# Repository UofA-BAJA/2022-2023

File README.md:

# Electrical Team 2022-2023
This is the codebase for the University of Arizona BAJA Electrical Team, year 2022/2023.

[Google Drive Link](https://drive.google.com/drive/folders/1pqr16L63S9_5N_NZjZeFR-gvrg_NTns5?usp=sharing)

**This years officers and members include:**
Alex Romero (Electrical Lead),
Michael Byerly (Father),
Oliver Sjostrom,
Alyssa Pomerleau,
Henry Overbeck,
Liam Neu,
Muthu Krishnappan,
Man Doan,
Aeden Grandinetti,
Dorian Shay,
Aliah Haigh,
Juliana Levy
...

**Languages include:**
Python (Ground Station Systems),
C++ (Telemetry System),

Pull Requests into the Main Branch can be approved by Alex or Michael.
We also have a Codigna review bot that will automatically grade our code and offer suggestions in order to improve performance or legibility.

If you have any questions regarding any pieces of software or their functionality, please reach out to the officers.

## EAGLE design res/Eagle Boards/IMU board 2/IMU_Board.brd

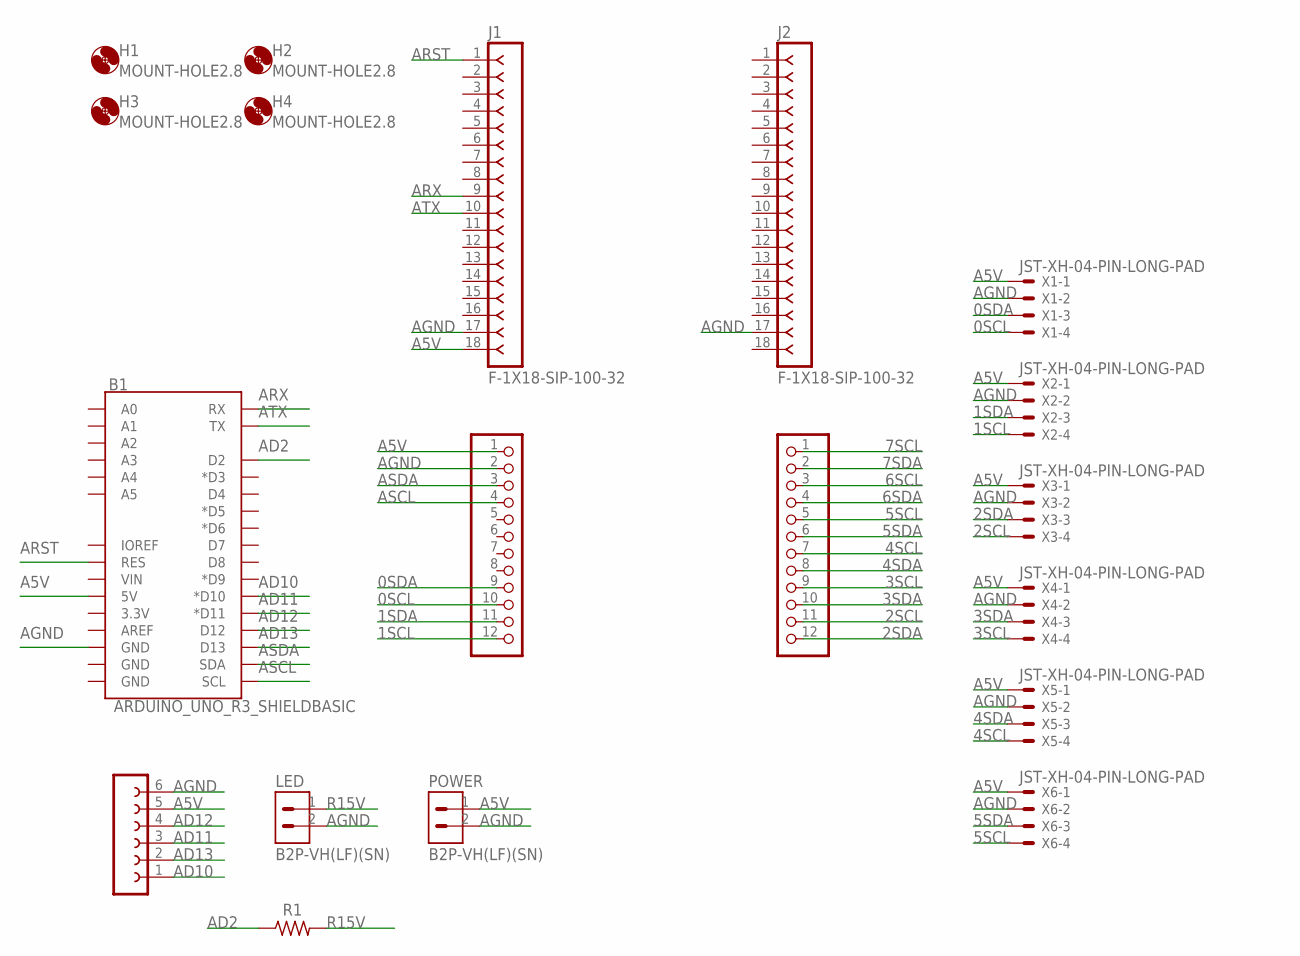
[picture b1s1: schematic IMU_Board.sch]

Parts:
B1: ARDUINO_UNO_R3_SHIELDBASIC; UNO_R3_SHIELD
H1, H2, H3, H4: MOUNT-HOLE2.8; 2,8
J1, J2: F-1X18-SIP-100-32; SIP-100-18-32
JP1, JP3: HEADER-1X12; 1X12_ROUND
LED: B2P-VH(LF)(SN); HDR-02
POWER: B2P-VH(LF)(SN); HDR-02
R1: R-US_AXIAL-11.7MM-PITCH; RESAD1176W63L850D250B
SD: FE06-1; FE06
X1, X2, X3, X4, X5, X6: JST-XH-04-PIN-LONG-PAD; JST-XH-04-PACKAGE-LONG-PAD

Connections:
0SCL: JP3.10, X1.4
0SDA: JP3.9, X1.3
1SCL: JP3.12, X2.4
1SDA: JP3.11, X2.3
2SCL: JP1.11, X3.4
2SDA: JP1.12, X3.3
3SCL: JP1.9, X4.4
3SDA: JP1.10, X4.3
4SCL: JP1.7, X5.4
4SDA: JP1.8, X5.3
5SCL: JP1.5, X6.4
5SDA: JP1.6, X6.3
6SCL: JP1.3
6SDA: JP1.4
7SCL: JP1.1
7SDA: JP1.2
A5V: B1.5V, J1.18, JP3.1, POWER.1, SD.5, X1.1, X2.1, X3.1, X4.1, X5.1, X6.1
AD2: B1.D2, R1.1
AD10: B1.D10 (*D10), SD.1
AD11: B1.D11 (*D11), SD.3
AD12: B1.D12, SD.4
AD13: B1.D13, SD.2
AGND: B1.GND@2 (GND), J1.17, J2.17, JP3.2, LED.2, POWER.2, SD.6, X1.2, X2.2, X3.2, X4.2, X5.2, X6.2
ARST: B1.RES, J1.1
ARX: B1.RX, J1.9
ASCL: B1.SCL, JP3.4
ASDA: B1.SDA, JP3.3
ATX: B1.TX, J1.10
R15V: LED.1, R1.2

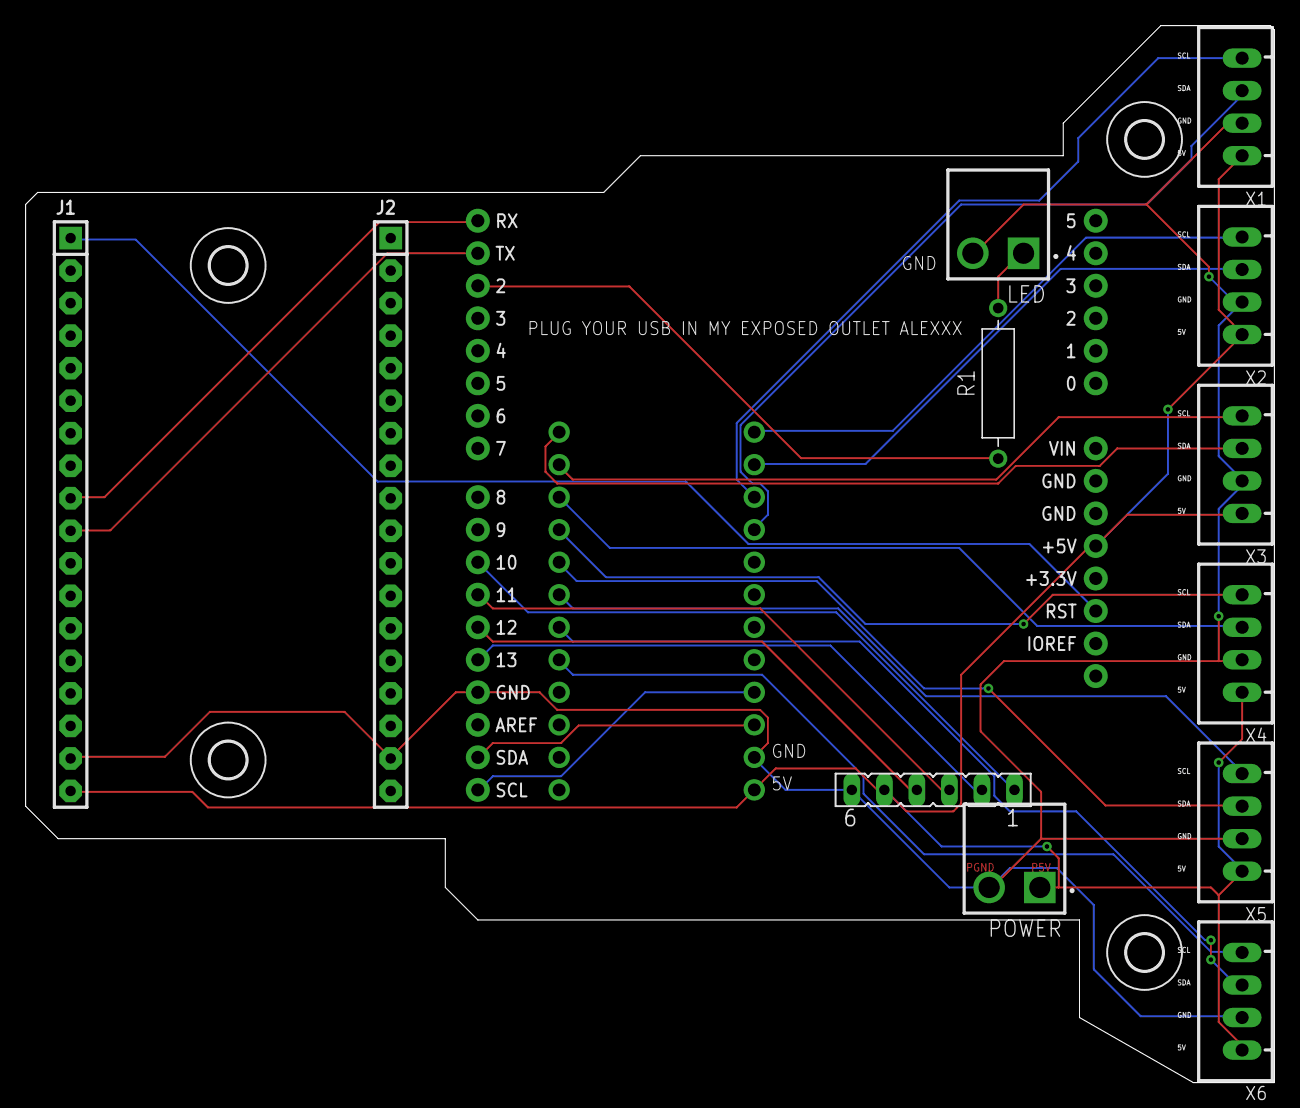
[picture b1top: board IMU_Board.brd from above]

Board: 2 copper layers, 97.5 x 82.5 mm, 19 parts (0 on the bottom side), 25 nets.

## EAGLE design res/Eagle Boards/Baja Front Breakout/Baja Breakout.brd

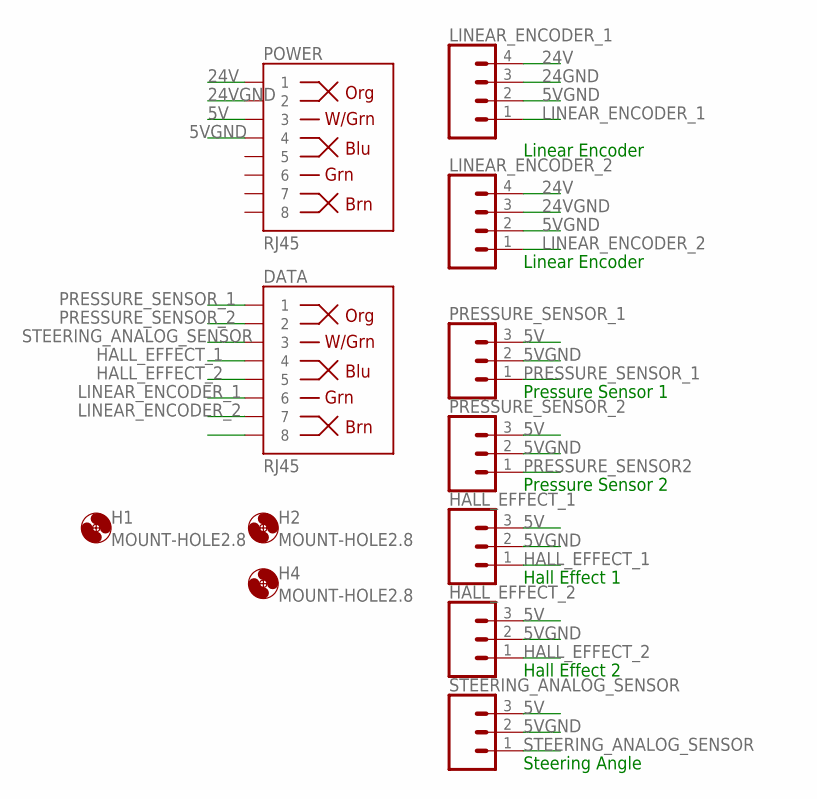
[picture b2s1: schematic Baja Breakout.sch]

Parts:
DATA: RJ45; RJ45-8
H1, H2, H4: MOUNT-HOLE2.8; 2,8
HALL_EFFECT_1, HALL_EFFECT_2: CONN_03; 1X03
LINEAR_ENCODER_1, LINEAR_ENCODER_2: CONN_04; 1X04
POWER: RJ45; RJ45-8
PRESSURE_SENSOR_1, PRESSURE_SENSOR_2: CONN_03; 1X03
STEERING_ANALOG_SENSOR: CONN_03; 1X03

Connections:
5V: HALL_EFFECT_1.3, HALL_EFFECT_2.3, POWER.3, PRESSURE_SENSOR_1.3, PRESSURE_SENSOR_2.3, STEERING_ANALOG_SENSOR.3
5VGND: HALL_EFFECT_1.2, HALL_EFFECT_2.2, LINEAR_ENCODER_1.2, LINEAR_ENCODER_2.2, POWER.4, PRESSURE_SENSOR_1.2, PRESSURE_SENSOR_2.2, STEERING_ANALOG_SENSOR.2
24GND: LINEAR_ENCODER_1.3
24V: LINEAR_ENCODER_1.4, LINEAR_ENCODER_2.4, POWER.1
24VGND: LINEAR_ENCODER_2.3, POWER.2
HALL_EFFECT_1: DATA.4, HALL_EFFECT_1.1
HALL_EFFECT_2: DATA.5, HALL_EFFECT_2.1
LINEAR_ENCODER_1: DATA.6, LINEAR_ENCODER_1.1
LINEAR_ENCODER_2: DATA.7, LINEAR_ENCODER_2.1
PRESSURE_SENSOR2: PRESSURE_SENSOR_2.1
PRESSURE_SENSOR_1: DATA.1, PRESSURE_SENSOR_1.1
PRESSURE_SENSOR_2: DATA.2
STEERING_ANALOG_SENSOR: DATA.3, STEERING_ANALOG_SENSOR.1

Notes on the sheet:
Linear Encoder
Pressure Sensor 2
Hall Effect 1
Hall Effect 2
Steering Angle
Pressure Sensor 1

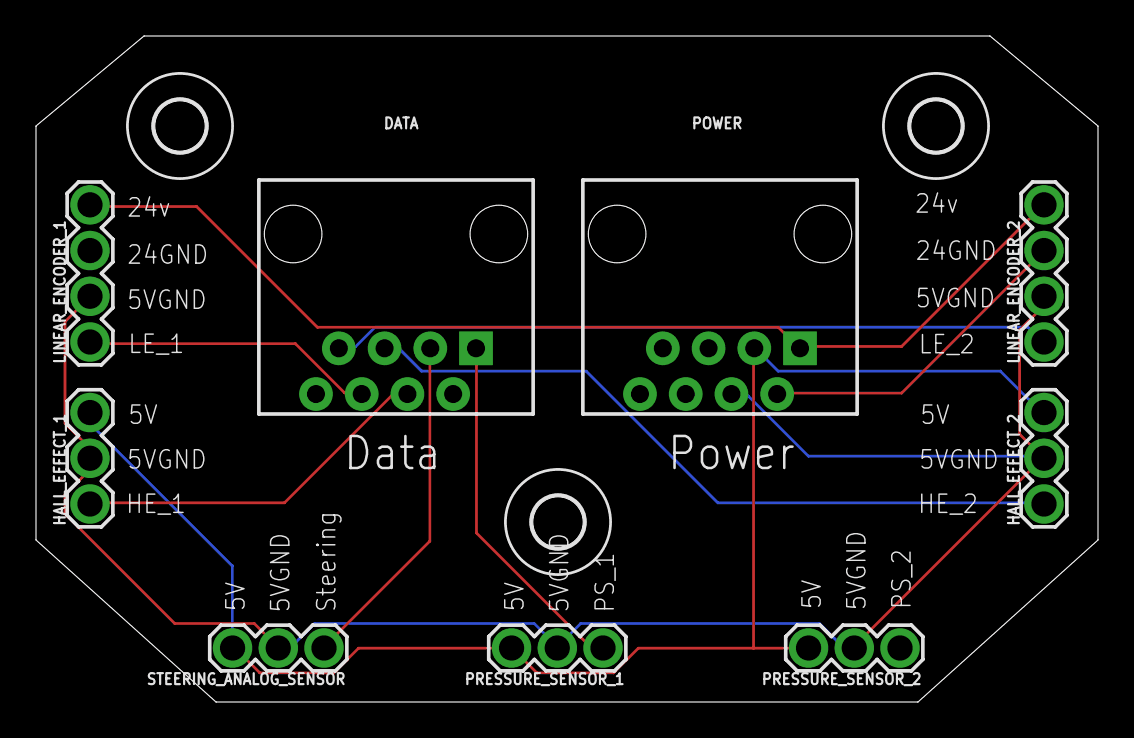
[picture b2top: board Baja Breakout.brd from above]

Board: 2 copper layers, 59.0 x 37.0 mm, 12 parts (0 on the bottom side), 10 nets.

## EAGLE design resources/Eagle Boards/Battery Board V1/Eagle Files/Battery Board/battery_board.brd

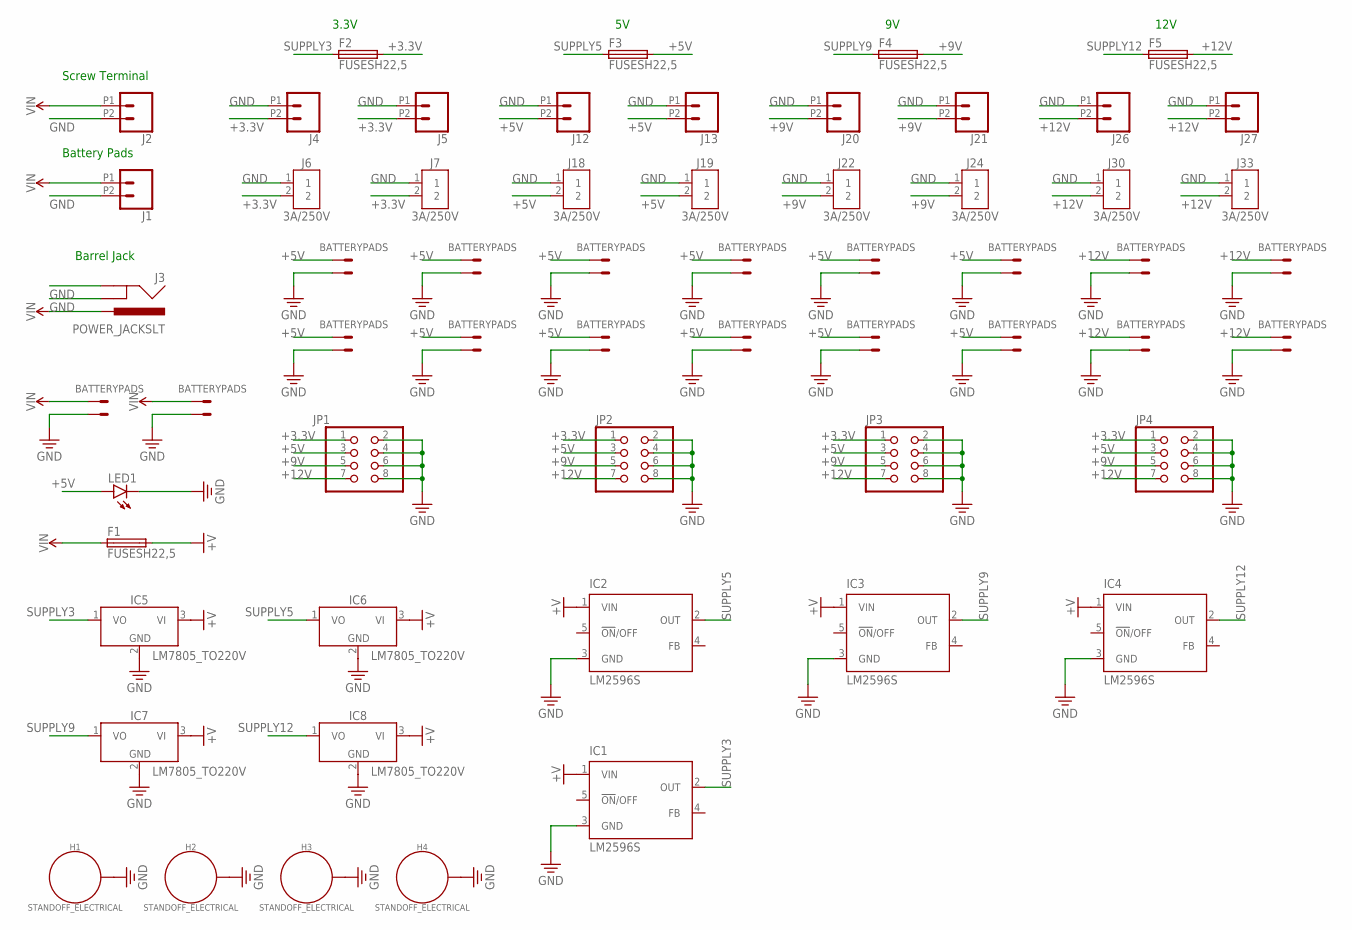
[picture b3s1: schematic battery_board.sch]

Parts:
BATTERY1, BATTERY2: BATTERYPADS; DIODFN1228X508X30-2N
F1, F2, F3, F4, F5: FUSESH22,5; SH22,5
H1, H2, H3, H4: STANDOFF_ELECTRICAL; STANDOFF-ELECTRICAL
IC1, IC2, IC3, IC4: LM2596S; TO263-5
IC5, IC6, IC7, IC8: LM7805_TO220V; TO220V
J1, J2, J4, J5, J12, J13, J20, J21, J26, J27: CONN_022.54MM_SCREWTERM; 1X02_2.54_SCREWTERM
J3: POWER_JACKSLT; POWER_JACK_SLOT
J6, J7, J18, J19, J22, J24, J30, J33: 3A/250V; B2B-XH-A
JP1, JP2, JP3, JP4: PINHD-2X4; 2X04
LED1: LEDCHIP-LED0805; CHIP-LED0805
U$1, U$2, U$3, U$4, U$5, U$6, U$7, U$8, U$9, U$10, U$11, U$12, U$13, U$14, U$15, U$16: BATTERYPADS; DIODFN1228X508X30-2N

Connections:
+3.3V: F2.2, J4.P2 (2), J5.P2 (2), J6.2, J7.2, JP1.1, JP2.1, JP3.1, JP4.1
+5V: F3.2, J12.P2 (2), J13.P2 (2), J18.2, J19.2, JP1.3, JP2.3, JP3.3, JP4.3, LED1.A, U$1.VIN, U$2.VIN, U$3.VIN, U$4.VIN, U$5.VIN, U$6.VIN, U$7.VIN, U$8.VIN, U$13.VIN, U$14.VIN, U$15.VIN, U$16.VIN
+9V: F4.2, J20.P2 (2), J21.P2 (2), J22.2, J24.2, JP1.5, JP2.5, JP3.5, JP4.5
+12V: F5.2, J26.P2 (2), J27.P2 (2), J30.2, J33.2, JP1.7, JP2.7, JP3.7, JP4.7, U$9.VIN, U$10.VIN, U$11.VIN, U$12.VIN
+V: F1.2, IC1.1 (VIN), IC2.1 (VIN), IC3.1 (VIN), IC4.1 (VIN), IC5.3 (VI), IC6.3 (VI), IC7.3 (VI), IC8.3 (VI)
GND: BATTERY1.GND, BATTERY2.GND, H1.P1, H2.P1, H3.P1, H4.P1, IC1.3 (GND), IC2.3 (GND), IC3.3 (GND), IC4.3 (GND), IC5.2 (GND), IC6.2 (GND), IC7.2 (GND), IC8.2 (GND), J1.P2 (2), J2.P2 (2), J3.GND@1 (GNDBREAK), J3.GND@2 (GND), J4.P1 (1), J5.P1 (1), J6.1, J7.1, J12.P1 (1), J13.P1 (1), J18.1, J19.1, J20.P1 (1), J21.P1 (1), J22.1, J24.1, J26.P1 (1), J27.P1 (1), J30.1, J33.1, JP1.2, JP1.4, JP1.6, JP1.8, JP2.2, JP2.4, JP2.6, JP2.8, JP3.2, JP3.4, JP3.6, JP3.8, JP4.2, JP4.4, JP4.6, JP4.8, LED1.C, U$1.GND, U$2.GND, U$3.GND, U$4.GND, U$5.GND, U$6.GND, U$7.GND, U$8.GND, U$9.GND, U$10.GND, U$11.GND, U$12.GND, U$13.GND, U$14.GND, U$15.GND, U$16.GND
SUPPLY3: F2.1, IC1.2 (OUT), IC5.1 (VO)
SUPPLY5: F3.1, IC2.2 (OUT), IC6.1 (VO)
SUPPLY9: F4.1, IC3.2 (OUT), IC7.1 (VO)
SUPPLY12: F5.1, IC4.2 (OUT), IC8.1 (VO)
VIN: BATTERY1.VIN, BATTERY2.VIN, F1.1, J1.P1 (1), J2.P1 (1), J3.PWR

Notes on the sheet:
Screw Terminal
Battery Pads
Barrel Jack
12V
3.3V

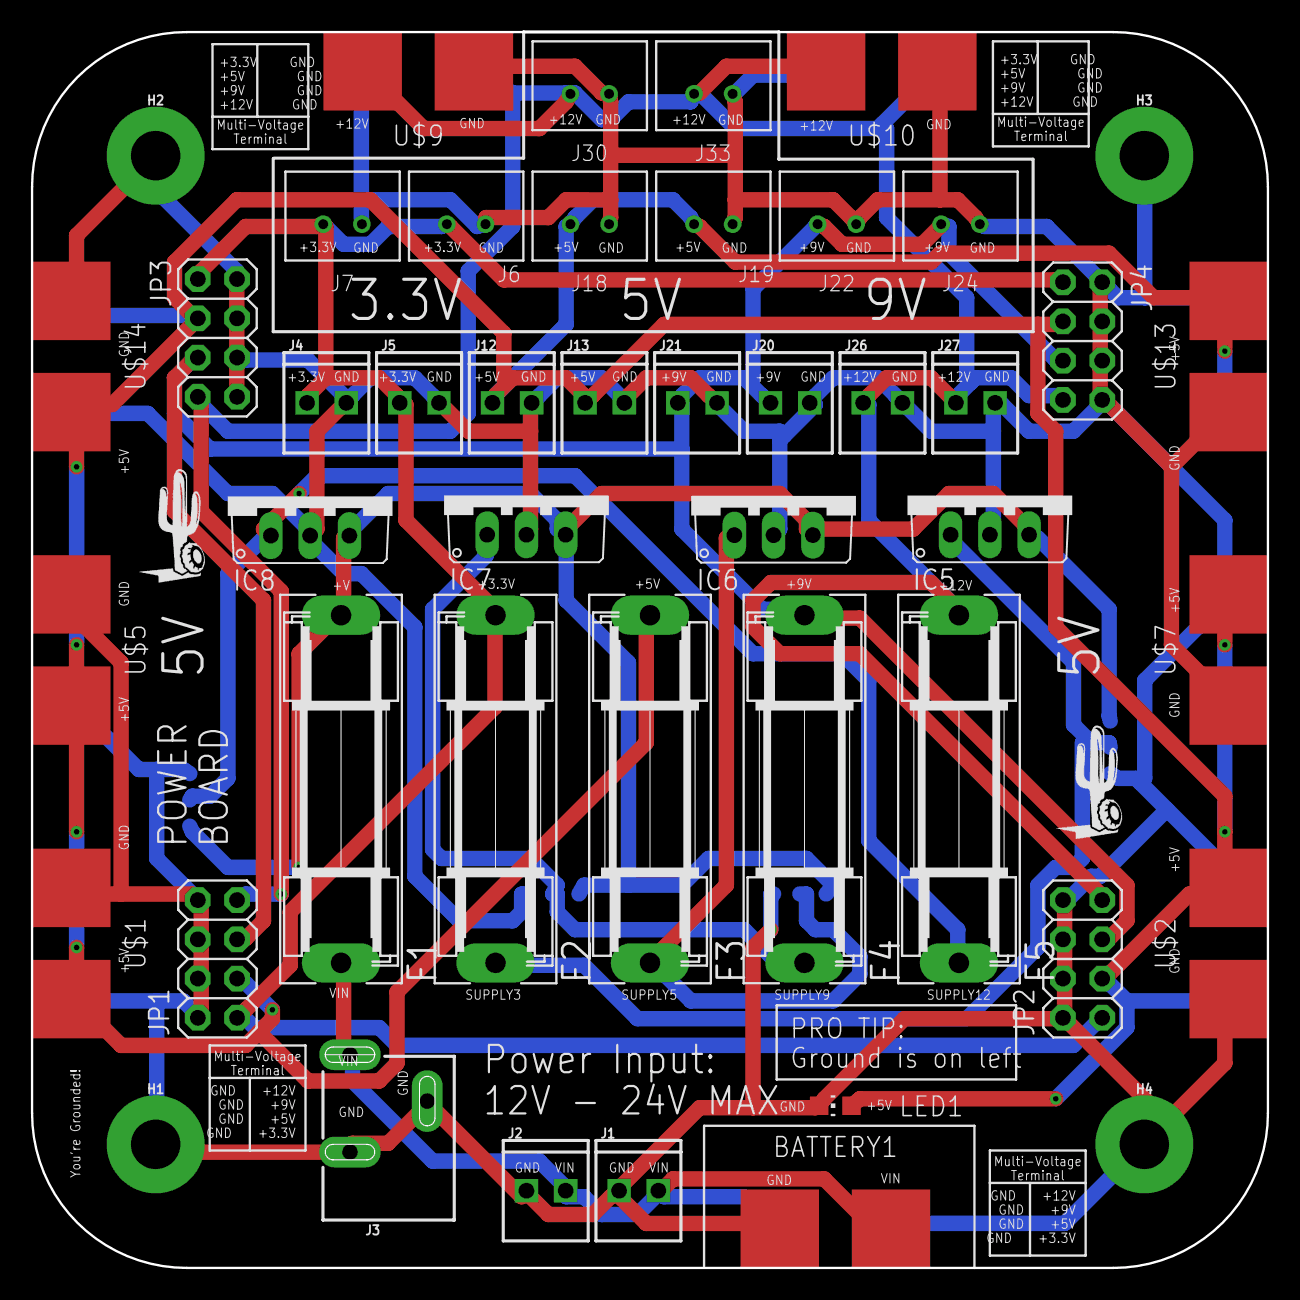
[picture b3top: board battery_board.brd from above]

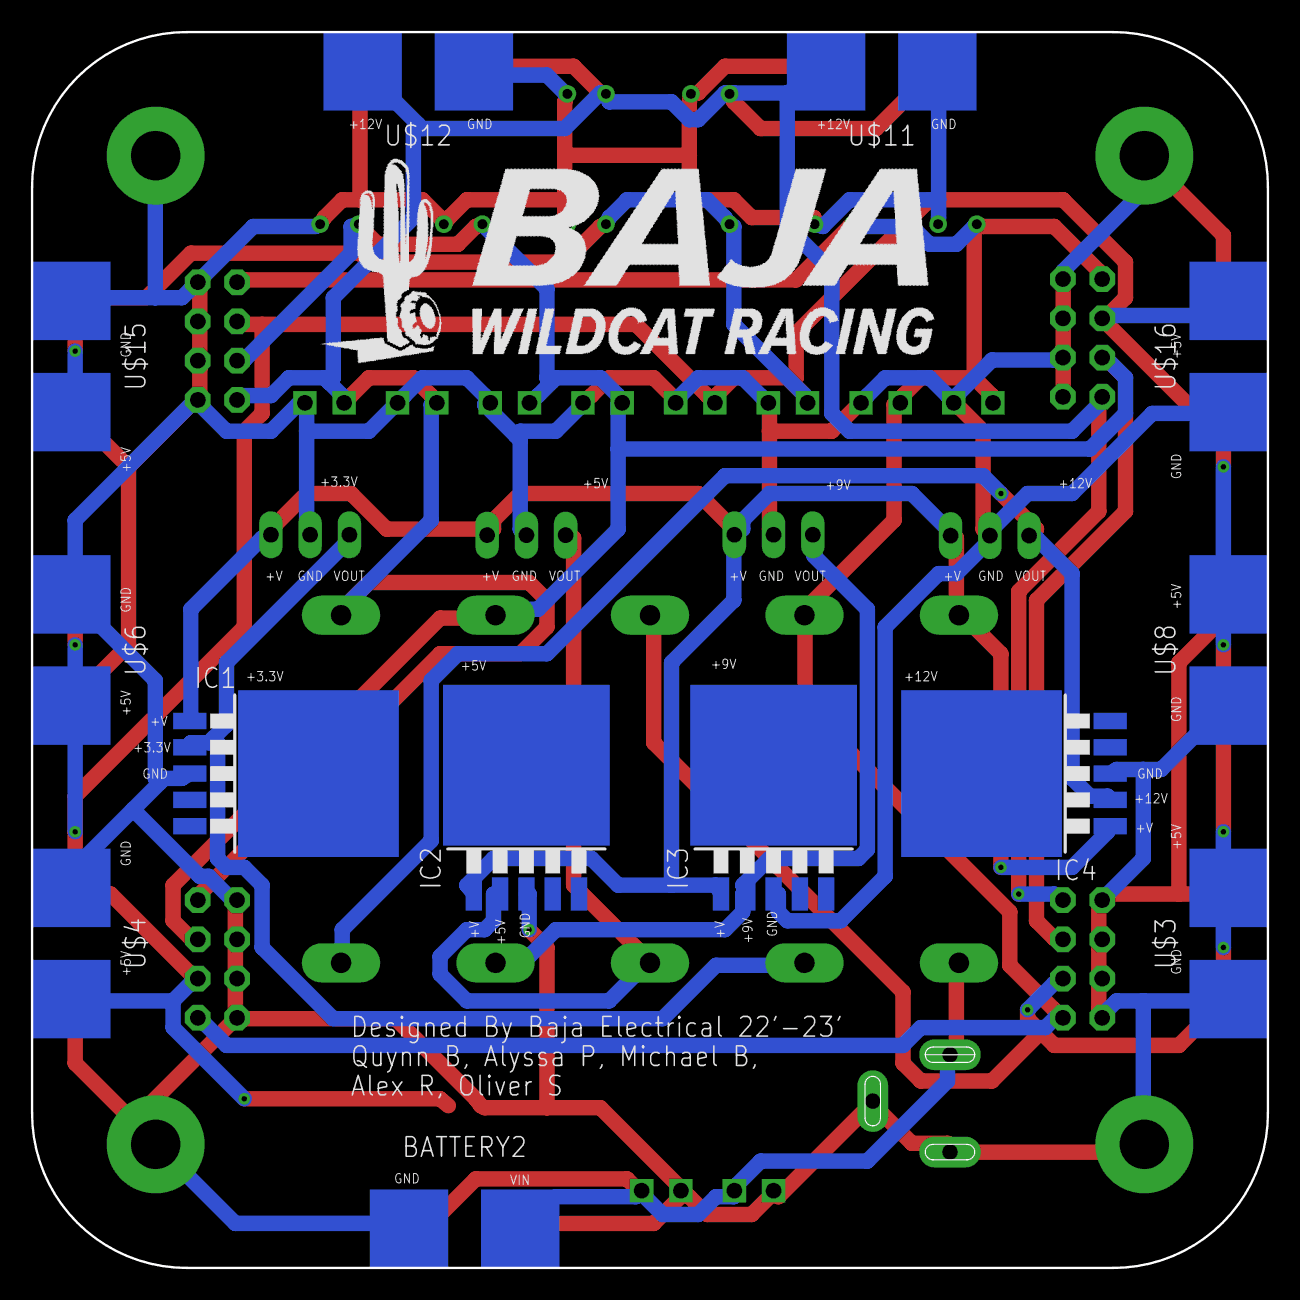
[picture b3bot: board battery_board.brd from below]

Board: 2 copper layers, 80.0 x 80.0 mm, 59 parts (13 on the bottom side), 11 nets.

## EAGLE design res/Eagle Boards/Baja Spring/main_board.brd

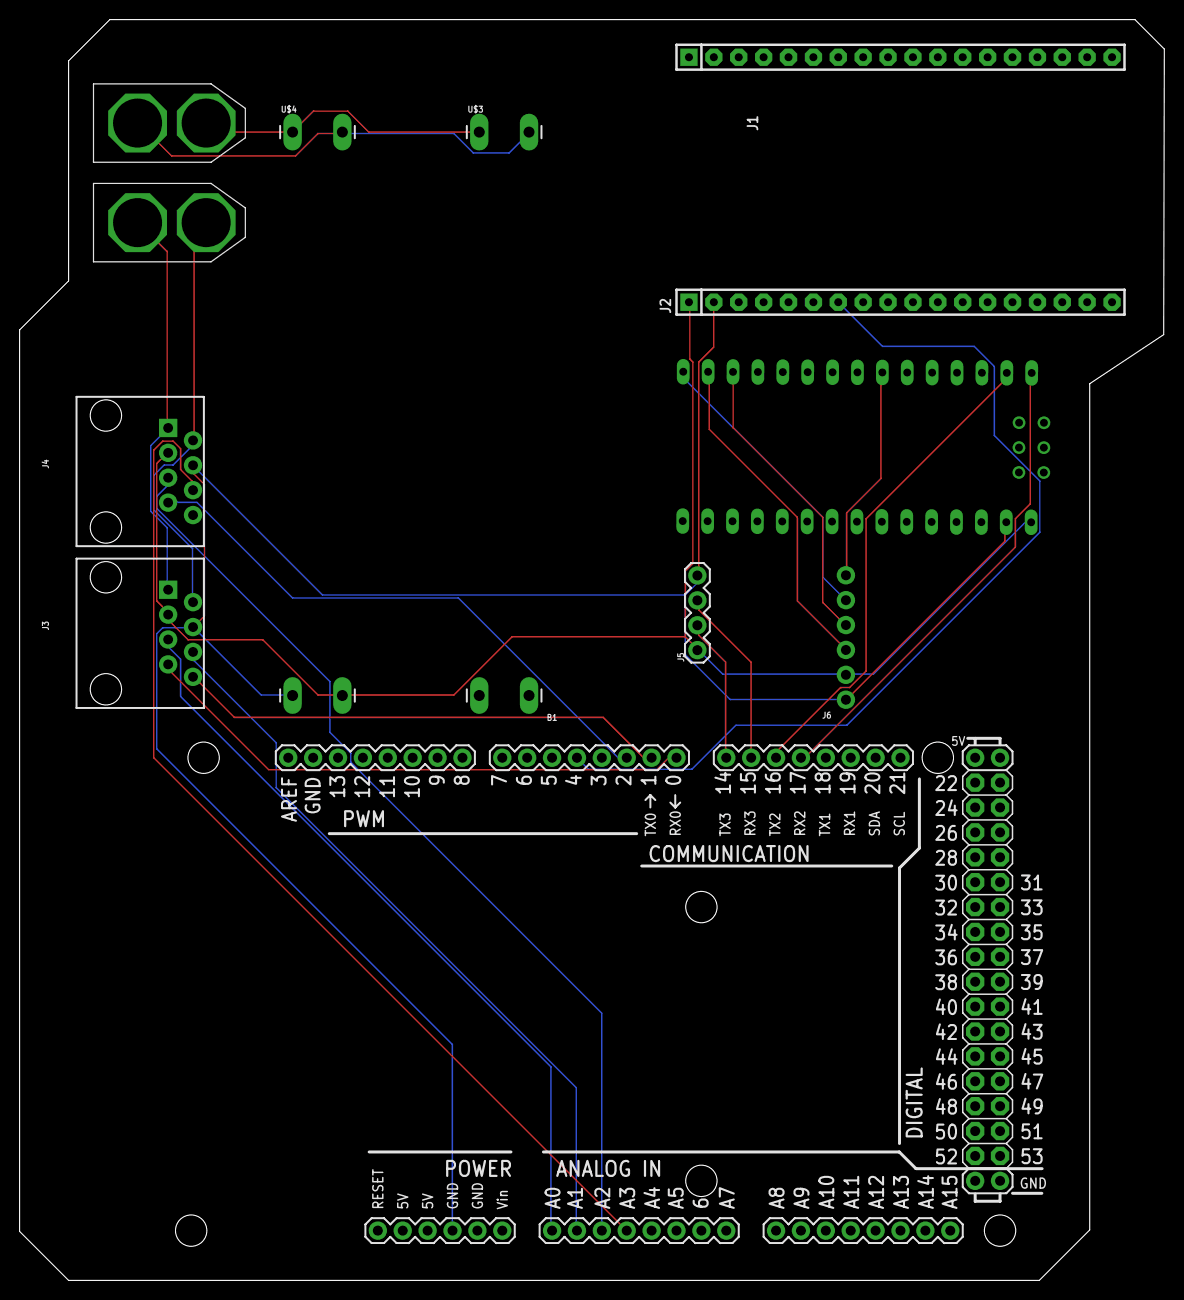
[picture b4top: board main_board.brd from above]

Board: 2 copper layers, 116.8 x 128.7 mm, 12 parts (0 on the bottom side), 22 nets.

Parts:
B1: ARDUINO_MEGA_R3FULL; ARDUINO_MEGA
J1, J2: F-1X18-SIP-100-32; SIP-100-18-32
J3, J4: RJ45; RJ45-8
J5: 1X04
J6: 1X06_NO_SILK
U$1: NANO
U$2, U$5: XT60
U$3, U$4: BUCKPINSBUCK; 1X03_LONGPADS

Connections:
5V: J2.1, J3.3, J4.3, J5.1, J6.2, U$1.RAW, U$4.VOUT+
5VGND: B1.GND@0, J2.2, J3.4, J4.4, J5.4, J6.1, U$1.GND, U$4.VOUT-
20V: U$2.+, U$3.VIN+, U$4.VIN+
20VGND: U$2.-, U$3.VIN-, U$4.VIN-
24V: J3.1, J4.1, U$5.+
24VGND: J3.2, J4.2, U$5.-
BUSY: B1.4, J2.7
CS: J6.6, U$1.D4
HALL_EFFECT_1: B1.0, J3.7
HALL_EFFECT_2: B1.1, J3.8
HALL_EFFECT_3: B1.2, J4.7
LINEAR_ENCODER_1: B1.A0, J3.5
LINEAR_ENCODER_2: B1.A1, J3.6
LINEAR_ENCODER_3: B1.A2, J4.5
LINEAR_ENCODER_4: B1.A3, J4.6
MEGARX2: B1.17, U$1.TX0
MEGARX3: B1.15, J5.3
MEGATX2: B1.16, U$1.RX1
MEGATX3: B1.14, J5.2
MISO: J6.3, U$1.D11
MOSI: J6.4, U$1.D10
SCK: J6.5, U$1.D12

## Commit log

2022-07-08 creating folders and base files
2022-07-08 test
2022-07-11 Adding more modules
2022-07-11 testing code review
2022-07-12 test code review
2022-07-12 test code review (#5)
2022-07-12 test #2
2022-07-13 very important message
2022-07-13 very important message (#7)
2022-07-13 fixing return issue
2022-07-13 fixing return issue (#11)
    * test code review
    * test #2
    * Add files via upload
    * Delete LoRa GPS Code directory
    * Add files via upload
    * very important message (#7)
2022-08-05 adding LoRa GPS examples
2022-08-05 adding product page
2022-08-05 adding more examples
2022-08-06 adding arduino ide into vs code
2022-08-06 testing uploading to LoRa GPS board
2022-08-06 finalizing changes for the day
2022-08-07 adding beta I2C communication methods
2022-08-08 Implementing I2C Handling
2022-08-20 Add files via upload
    Basic send GPS over Lora testing code
2022-08-28 imu code for all 6 imus to work
    tested in shop works good
2022-10-10 Adding Power Board Files
2022-10-22 Create code dump
2022-10-22 Create poop
2023-01-08 WE GONNA GET IT GOINGGGG
2023-01-09 yabagagoo
2023-01-09 yessirr
2023-01-09 we graping
2023-01-09 asdasd
2023-01-09 added arduino code
    this code is literally beautiful
2023-01-15 added the imu code and the python code (#19)
    * Add files via upload
    * WE GONNA GET IT GOINGGGG
    * yabagagoo
    * yessirr
    * we graping
    * asdasd
2023-01-15 Addition of Arduino Code (#20)
    * Add files via upload
    * WE GONNA GET IT GOINGGGG
    * yabagagoo
    * yessirr
    * we graping
    * asdasd
2023-01-28 Create description
2023-02-04 Update description
2023-02-10 Updating Main Branch (#14)
    * test code review
    * test #2
    * Add files via upload
    * Delete LoRa GPS Code directory
    * Add files via upload
    * very important message (#7)
2023-02-10 restructuring github
2023-02-10 restructuring of files (#21)
    * Add files via upload
    * WE GONNA GET IT GOINGGGG
    * yabagagoo
    * yessirr
    * we graping
    * asdasd
2023-02-10 updating some more
2023-02-10 forgot to get upstream (#22)
    * Add files via upload
    * WE GONNA GET IT GOINGGGG
    * yabagagoo
    * yessirr
    * we graping
    * asdasd
2023-02-10 still restructuring (#26)
    * Add files via upload
    * WE GONNA GET IT GOINGGGG
    * yabagagoo
    * yessirr
    * we graping
    * asdasd
2023-02-10 tech issues (#28)
    * Add files via upload
    * WE GONNA GET IT GOINGGGG
    * yabagagoo
    * yessirr
    * we graping
    * asdasd
2023-02-10 something
2023-02-10 maybe this works (#29)
    * fixing return issue (#11)
    * test code review
    * test #2
    * Add files via upload
    * Delete LoRa GPS Code directory
    * Add files via upload
2023-02-10 Restucturing files (#32)
    * Delete main.cpp
    * Delete strain.cpp
    ---------
2023-02-10 deleting
2023-02-10 deleting (#33)
2023-02-10 moving file
2023-02-10 moving file (#34)
2023-02-10 updating everything (#35)
    * deleting
    * moving file
2023-02-10 does this update anything (#36)
    * deleting
    * moving file
2023-02-10 literally anything (#37)
    * deleting
    * moving file
2023-02-10 initial pyqt interface
2023-02-10 its gonna get messy in here
2023-02-10 im lost
2023-02-10 getting something going
2023-02-10 kinda working
2023-02-10 building it out
2023-02-10 chugging
2023-02-10 its workingggg
2023-02-11 adding imu code
2023-02-11 adding imu code (#38)
2023-02-11 Add files via upload
    this is the lora reciver code AND the serial reciever, combine them
2023-02-11 moving into folder
2023-02-11 Pyqt interface (#39)
    * its gonna get messy in here
    * im lost
    * getting something going
    * kinda working
    * building it out
    * chugging
2023-02-11 Add files via upload (#40)
    this is the lora reciver code AND the serial reciever, combine them
2023-02-11 Mega to htc boards serial com (#41)
    * Add files via upload
    this is the lora reciver code AND the serial reciever, combine them
    * Update main.ino
    ---------
2023-02-11 Pyqt interface (#42)
    * its gonna get messy in here
    * im lost
    * getting something going
    * kinda working
    * building it out
    * chugging
2023-02-11 askdnasd
2023-02-11 asdj
2023-02-11 Dorian (#43)
    * askdnasd
    * asdj
2023-02-11 I fixed Alex's stupid lists
2023-02-11 Py qt interface (#44)
    * askdnasd
    * asdj
    * I fixed Alex's stupid lists
2023-02-13 reorganizing files
2023-02-13 Rename read.md to readme.md
2023-02-16 Py qt interface (#45)
    * askdnasd
    * asdj
    * I fixed Alex's stupid lists
    ---------
2023-02-18 poop
2023-02-18 Py qt interface (#46)
    * askdnasd
    * asdj
    * I fixed Alex's stupid lists
2023-02-18 i delete extra new lines
2023-02-18 Dorian branch (#47)
    * askdnasd
    * i delete extra new lines
2023-02-18 Added a hertz graph and class
    Alex wants my mom bad.
2023-02-18 Hz monitor (#48)
    * askdnasd
    * i delete extra new lines
    * Added a hertz graph and class
    Alex wants my mom bad.
2023-02-19 lordy
2023-02-25 possibly working
2023-02-25 possibly working (#50)
2023-02-25 Create readme.md (#51)
2023-02-25 updating gps (#52)
    * askdnasd
    * Py qt interface (#46)
    * askdnasd
    * asdj
    * I fixed Alex's stupid lists
    * i delete extra new lines
2023-02-25 Gps (#53)
    * poop
    * updating gps (#52)
    * askdnasd
    * Py qt interface (#46)
    * askdnasd
    * asdj
2023-02-25 Gps (#54)
    * poop
    * updating gps (#52)
    * askdnasd
    * Py qt interface (#46)
    * askdnasd
    * asdj
2023-02-25 updating gps again (#55)
    * askdnasd
    * Py qt interface (#46)
    * askdnasd
    * asdj
    * I fixed Alex's stupid lists
    * i delete extra new lines
2023-02-25 adding diagrams
2023-02-25 getting rid of proces(text)
2023-02-25 tada
2023-02-25 hmmm
2023-02-25 yesirr
2023-02-25 messing about
2023-02-25 poopy mc poopy
2023-02-26 poopy
2023-02-26 DATABASE ADDED
2023-02-26 leets goo
2023-02-26 lots of commits
2023-02-26 dang
2023-02-27 goodnight github
2023-02-27 bedtime
2023-02-27 now goodnight fr
2023-02-27 moving files
2023-03-01 classes on classes
2023-03-03 big ol commit
2023-03-03 Widget restrcuturing (#56)
    * tada
    * hmmm
    * yesirr
    * poop
    * messing about
    * lordy
2023-03-04 goddamn
2023-03-04 Widget restrcuturing (#57)
    * tada
    * hmmm
    * yesirr
    * poop
    * messing about
    * lordy
2023-03-04 updating gps branch (#59)
    * askdnasd
    * Py qt interface (#46)
    * askdnasd
    * asdj
    * I fixed Alex's stupid lists
    * i delete extra new lines
2023-03-04 shutup
2023-03-04 Widget restrcuturing (#60)
    * tada
    * hmmm
    * yesirr
    * poop
    * messing about
    * lordy
2023-03-04 dadad (#61)
    * askdnasd
    * Py qt interface (#46)
    * askdnasd
    * asdj
    * I fixed Alex's stupid lists
    * i delete extra new lines
2023-03-05 kmbjkbnkjbn
2023-03-05 getting rid of pycaches
2023-03-06 nutz
2023-03-12 teehee
2023-03-12 Added graphs
2023-03-12 Added graphs (#62)
2023-03-12 updating gps (#63)
    * askdnasd
    * Py qt interface (#46)
    * askdnasd
    * asdj
    * I fixed Alex's stupid lists
    * i delete extra new lines
2023-03-12 added a set up method
2023-03-12 Gps (#64)
    * updating gps (#63)
    * askdnasd
    * Py qt interface (#46)
    * askdnasd
    * asdj
    * I fixed Alex's stupid lists
2023-03-12 messing with fake gps
2023-03-13 yesssir
2023-03-13 Gps (#65)
    * updating gps (#63)
    * askdnasd
    * Py qt interface (#46)
    * askdnasd
    * asdj
    * I fixed Alex's stupid lists
2023-03-13 cleaing up gps stuff
2023-03-13 added the binary parsing file ive been using
2023-03-16 no more disabled tabs
2023-03-16 dangity dang
2023-03-18 IT WOKD
2023-03-19 time to make pyqt work
2023-03-19 updating serial parser (#66)
    * dadad (#61)
    * askdnasd
    * Py qt interface (#46)
    * askdnasd
    * asdj
    * I fixed Alex's stupid lists
2023-03-19 not working
2023-03-19 so many changes
2023-03-19 files are opening
2023-03-19 yurr
2023-03-19 yuhh
2023-03-20 teehe
2023-03-25 working min and max
2023-03-25 yesssirr
2023-03-25 working min and max (#67)
2023-03-25 asdads
2023-03-25 New serial parser (#68)
    * updating serial parser (#66)
    * dadad (#61)
    * askdnasd
    * Py qt interface (#46)
    * askdnasd
    * asdj
2023-03-25 added git ignore
2023-03-25 clickity clack
2023-04-03 board svgs
2023-04-04 penis
2023-04-04 penis (#69)
2023-04-04 reorganized files
2023-04-04 no pycache
2023-04-04 less goo
2023-04-04 yepp
2023-04-04 asas
2023-04-04 clean up
2023-04-04 jsonnnnn
2023-04-05 updating files
2023-04-07 gotta add the jsons first
2023-04-07 ehehhhehhehehehe
2023-04-07 ok ok
2023-04-07 made a really bad solution (#73)
2023-04-08 even worse solution
2023-04-08 begin
2023-04-08 fixed bug in csv parser
2023-04-08 test commit
2023-04-08 Jacob boushaki/issue71 (#74)
    * begin
    * asdasd
    * test commit
    ---------
2023-04-08 hmmmm
2023-04-08 cleaining up print statements
2023-04-08 afafa
2023-04-08 uodate
2023-04-08 hjgj
2023-04-08 fuck u
2023-04-08 New extra data (#76)
    * Update .gitignore
    * working min and max (#67)
    * New serial parser (#68)
    * updating serial parser (#66)
    * dadad (#61)
    * askdnasd
2023-04-08 fixed
2023-04-08 update git ignore
2023-04-08 trying to get a tare
2023-04-08 deleting boards
2023-04-14 idk wtf is wrong
2023-04-14 oppsie
2023-04-14 ik ik
2023-07-12 updating name

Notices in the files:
parts and their libraries:
SparkFun-Connectors: Licensing: Creative Commons ShareAlike 4.0 International - https://creativecommons.org/licenses/by-sa/4.0
con-headers-jp: Copyright (C) 2008, Bob Starr
